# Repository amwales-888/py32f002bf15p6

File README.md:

# py32f002bf15p6
Simple breakout board for py32f002bf15p6 tssop20 24MHz 24kB Flash 2kB Ram 18 IOs MCU

- 3.3v LDO powered from 5V USB.
- UART connectivity to USB via ch340 optionally connected to pins PA6/PA7 using jumpers.
- ARM SWD programming interface header.
- All other pins are broken out to headers.
- 1 LED optionally connected to pin PB4 using jumper.
- 1 Button with pulldown optionally connected to pin PB5 using jumper.
- 1 Button connected to RESET pin, pulled high.

<table>
  <tr>
    <td> </td>
    <td> </td>
  </tr>
  <tr>
    <td> </td>
    <td> </td>
  </tr>
</table>

Resources

<li>https://www.puyasemi.com/en/py32_series.html</li>
<li>https://www.eevblog.com/forum/microcontrollers/$0-11-py32f002a-m0-24mhz-320kb-actually-324kb-more-peripherals/</li>
<li>https://www.cnblogs.com/milton/p/18168592</li>
<li>https://github.com/IOsetting/py32f0-template/tree/main</li>
<li>https://www.cnblogs.com/milton/p/17111286.html</li>
<li>https://www.cnblogs.com/milton/p/18168592</li>
<li>https://www.lcsc.com/product-detail/C7469098.html</li>

<BR>

Notes - The attached firmware was written for the deprecated board produced with EAGLE, since then I have replaced the 
oscillator with a crystal and may have changed the IO pin for LED0/SW0 review the code before using it. I will update 
it when I have time.

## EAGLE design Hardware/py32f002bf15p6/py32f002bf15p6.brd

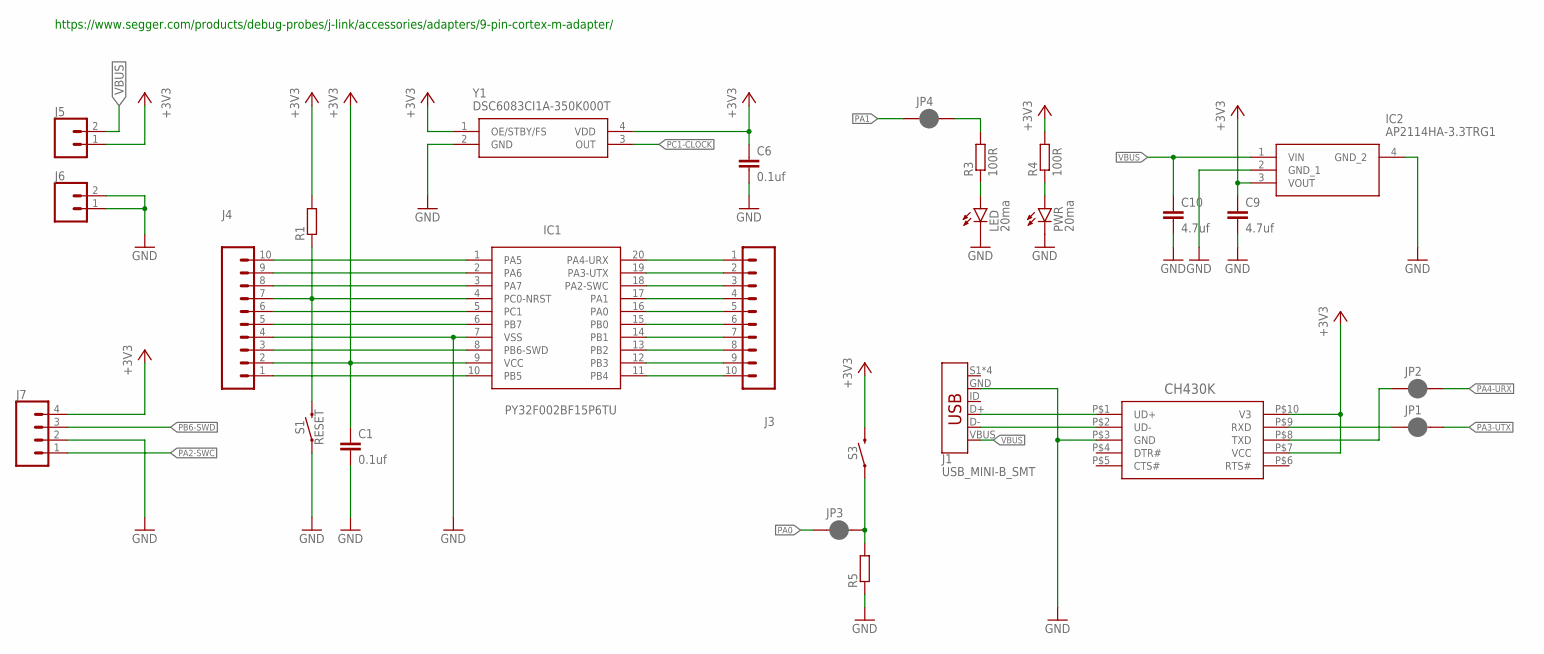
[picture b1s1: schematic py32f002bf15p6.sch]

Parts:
C1, C6: 0.1uf; C0805
C9, C10: 4.7uf; C1206
IC1: PY32F002BF15P6TU; TSSOP20
IC2: AP2114HA-3.3TRG1; SOT230P700X180-4N
J1: USB_MINI-B_SMT; USB-MINIB
J3, J4: CONN_10"; 1X10
J5, J6: CONN_02; 1X02
J7: CONN_04PTH; 1X04
JP1, JP2, JP3, JP4: JUMPER-SMT_2_NC_PASTE_SILK; SMT-JUMPER_2_NC_PASTE_SILK
LED: 20ma; SML0805
PWR: 20ma; SML0805
R1, R5: R-EU_R0805; R0805
R3, R4: 100R; R0805
S1, S3: RESET; TACTILE_SWITCH_SMD_6.0X3.5MM
U$1: CH430K; ESSOP-10
Y1: DSC6083CI1A-350K000T; DSC6083CI1A350K000T

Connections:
+3V3: C1.1, C6.1, C9.1, IC1.9 (VCC), IC2.3 (VOUT), J4.2, J5.1, J7.4, R1.2, R4.2, S3.2, U$1.P$7 (VCC), U$1.P$10 (V3), Y1.1 (OE/STBY/FS), Y1.4 (VDD)
GND: C1.2, C6.2, C9.2, C10.2, IC1.7 (VSS), IC2.2 (GND_1), IC2.4 (GND_2), J1.GND, J4.4, J6.1, J6.2, J7.2, LED.C, PWR.C, R5.1, S1.1, U$1.P$3 (GND), Y1.2 (GND)
unnamed: JP3.2, R5.2, S3.1
unnamed: LED.A, R3.1
unnamed: JP4.2, R3.2
unnamed: PWR.A, R4.1
PA0: IC1.16 (PA0), J3.5, JP3.1
PA1: IC1.17 (PA1), J3.4, JP4.1
PA2-SWC: IC1.18 (PA2-SWC), J3.3, J7.1
PA3-UTX: IC1.19 (PA3-UTX), J3.2, JP1.2
PA4-URX: IC1.20 (PA4-URX), J3.1, JP2.2
PA5: IC1.1 (PA5), J4.10
PA6: IC1.2 (PA6), J4.9
PA7: IC1.3 (PA7), J4.8
PB0: IC1.15 (PB0), J3.6
PB1: IC1.14 (PB1), J3.7
PB2: IC1.13 (PB2), J3.8
PB3: IC1.12 (PB3), J3.9
PB4: IC1.11 (PB4), J3.10
PB5: IC1.10 (PB5), J4.1
PB6-SWD: IC1.8 (PB6-SWD), J4.3, J7.3
PB7: IC1.6 (PB7), J4.5
PC0-RST: IC1.4 (PC0-NRST), J4.7, R1.1, S1.2
PC1-CLOCK: IC1.5 (PC1), J4.6, Y1.3 (OUT)
RXD: JP1.1, U$1.P$9 (RXD)
TXD: JP2.1, U$1.P$8 (TXD)
USB_N: J1.D-, U$1.P$2 (UD-)
USB_P: J1.D+, U$1.P$1 (UD+)
VBUS: C10.1, IC2.1 (VIN), J1.VBUS, J5.2

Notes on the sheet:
https://www.segger.com/products/debug-probes/j-link/accessories/adapters/9-pin-cortex-m-adapter/

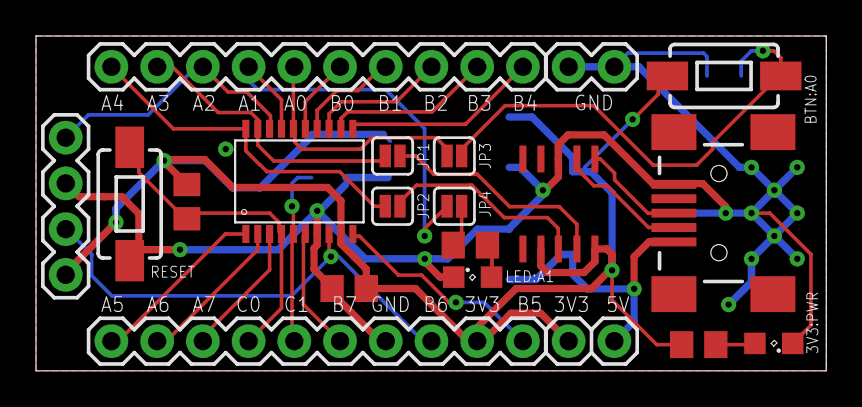
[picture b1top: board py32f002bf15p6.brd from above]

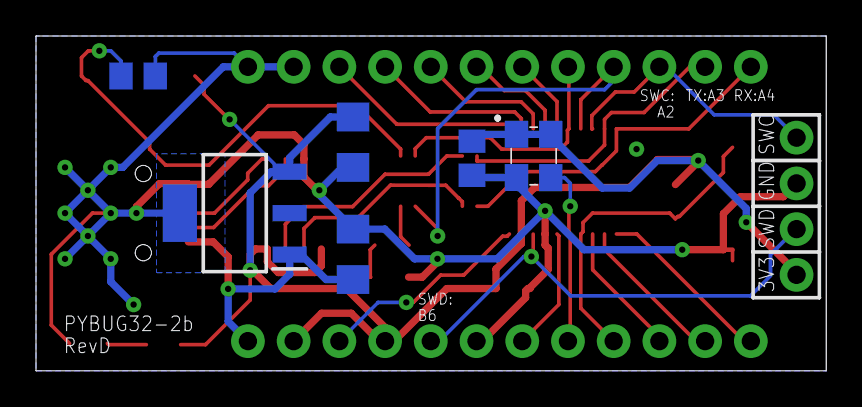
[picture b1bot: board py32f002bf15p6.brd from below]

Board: 2 copper layers, 43.9 x 18.6 mm, 26 parts (6 on the bottom side), 29 nets.

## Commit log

2024-08-14 Initial Checkin
2024-08-31 Final Draft
2024-09-03 Looks likes I screwed up UART TX/RX pins
    Looks likes I screwed up UART TX/RX pins - im blaming submitting the board after returning from holiday before rechecking
2024-09-10 Ensure button is pulled down
    Ensure button is pulled down
2024-09-13 Added simple demo that toggles LED and send output to serial at 9600,8,n,1 through attached USB/Serial interface chip
2024-09-13 Generate final gerbers and rename directories to match chip name
2024-09-13 remove old file
2024-09-20 Replaced 4.7uf 0805 caps for larger 1206 parts
2024-09-27 Updated silkscreen, removed reset header pin
2024-09-29 Rename directories to match other py32 project
2026-04-24 Reformat Directory Structure and Add KiCAD version
    Reformat Directory Structure and Add KiCAD version
2026-04-24 Update README with corrected pin connections and images
2026-04-24 Change silkscreen and update gerbers
2026-04-24 Deprecated old eagle layout
    Deprecated old eagle layout
2026-04-25 Update README with new resource links
    Added additional resources for the py32 series.
2026-04-25 Update README with firmware notes
    Added notes about firmware compatibility and changes.
2026-04-25 Add LCSC product link to README
    Added a new link to LCSC product detail in the README.

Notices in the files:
parts and their libraries:
SparkFun-Switches: Licensing: Creative Commons ShareAlike 4.0 International - https://creativecommons.org/licenses/by-sa/4.0
